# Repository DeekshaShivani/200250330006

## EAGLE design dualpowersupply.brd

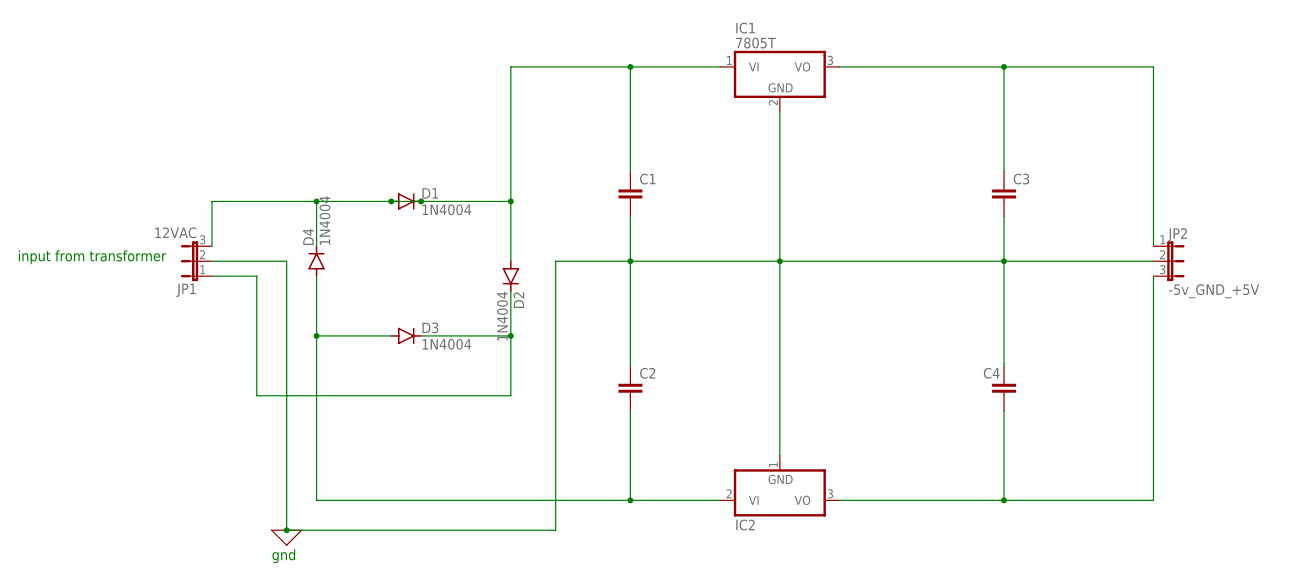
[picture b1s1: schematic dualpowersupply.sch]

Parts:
C1, C2, C3, C4: C2,5-3; C2.5-3
D1, D2, D3, D4: 1N4004; DO41-10
IC1: 7805T; TO220H
IC2: 7905T; TO220H
JP1: 12VAC; JP2W
JP2: -5v_GND_+5V; JP2W

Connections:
0: C1.2, C2.1, C3.2, C4.1, IC1.2 (GND), IC2.1 (GND), JP1.2, JP2.2
unnamed: C1.1, D1.A, D1.C, D2.A, D4.C, IC1.1 (VI), JP1.3
unnamed: C2.2, D3.A, D4.A, IC2.2 (VI)
unnamed: D2.C, D3.C, JP1.1
unnamed: C3.1, IC1.3 (VO), JP2.1
unnamed: C4.2, IC2.3 (VO), JP2.3

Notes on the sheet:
gnd
input from transformer

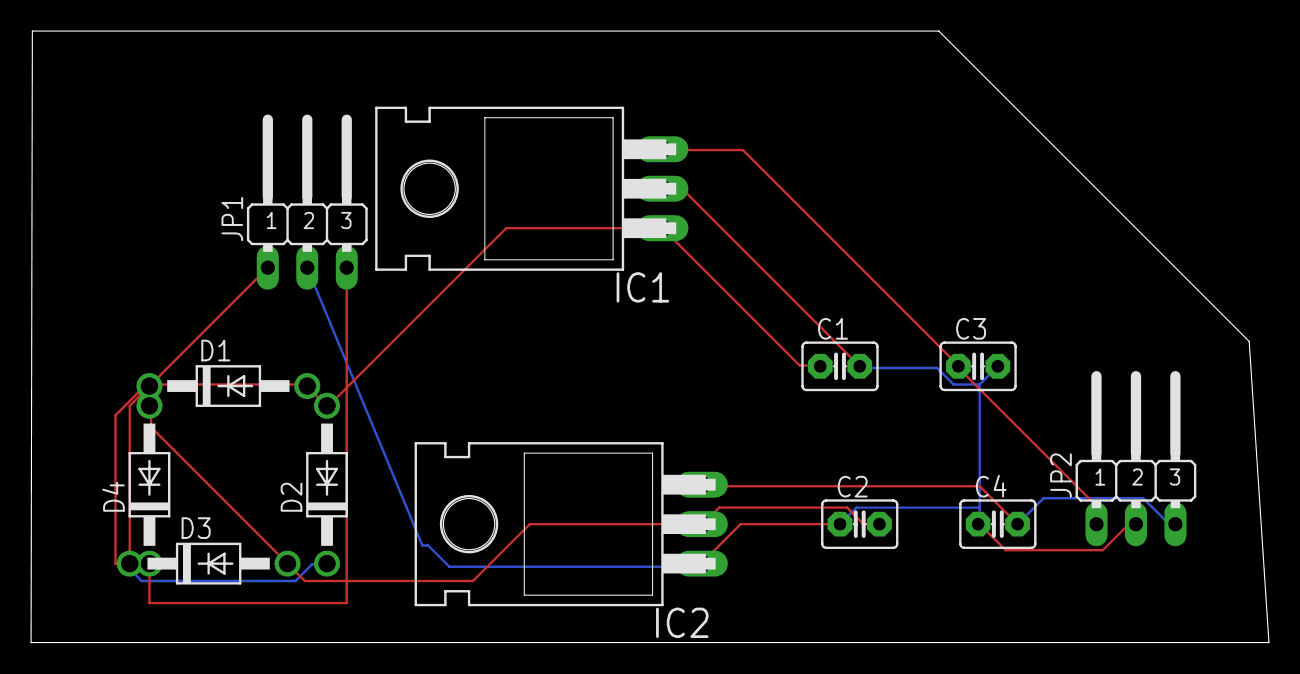
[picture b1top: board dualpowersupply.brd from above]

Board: 2 copper layers, 79.7 x 39.4 mm, 12 parts (0 on the bottom side), 6 nets.

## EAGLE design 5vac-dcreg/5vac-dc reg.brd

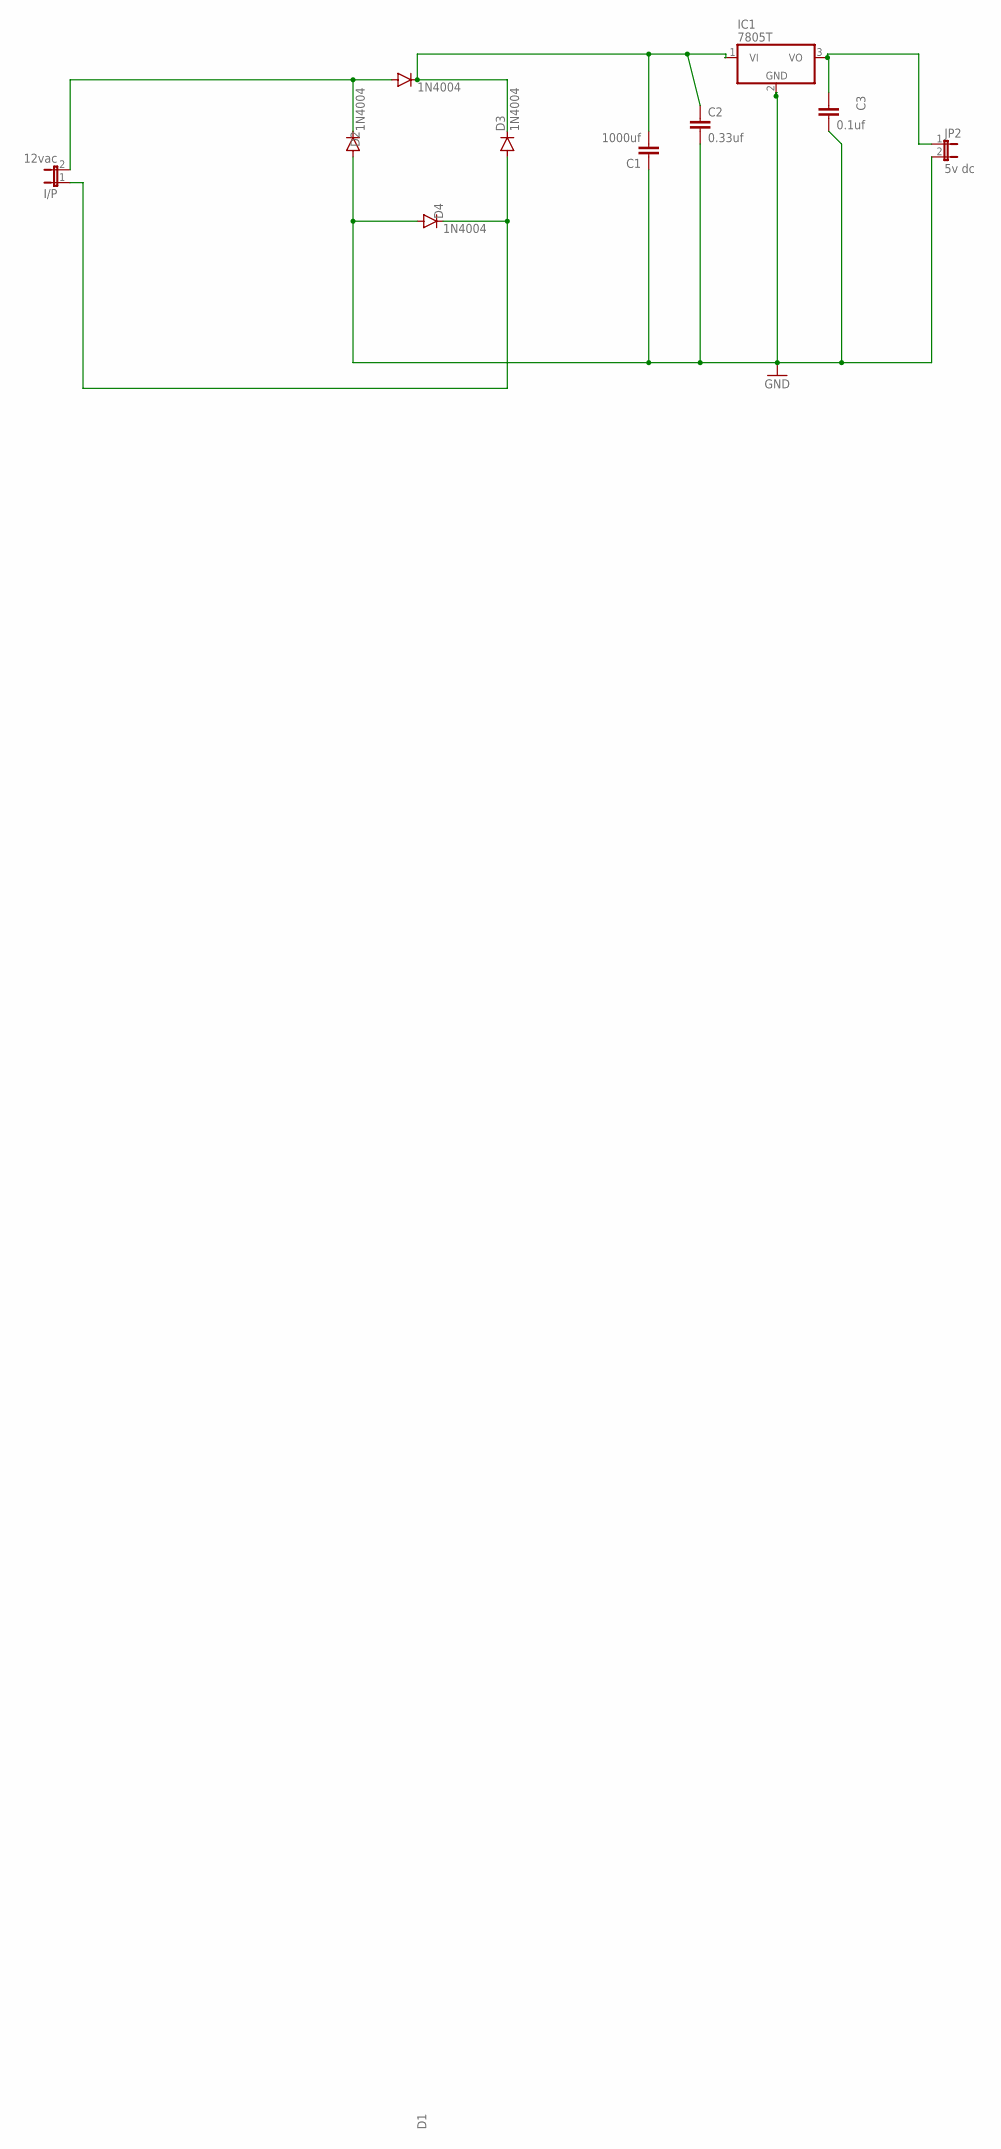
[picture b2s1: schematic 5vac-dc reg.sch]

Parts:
C1: 1000uf; C2.5-3
C2: 0.33uf; C2.5-3
C3: 0.1uf; C2.5-3
D1, D2, D3, D4: 1N4004; DO41-10
I/P: 12vac; JP1
IC1: 7805T; TO220H
JP2: 5v dc; JP1

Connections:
GND: C1.1, C2.2, C3.2, D2.A, D4.A, IC1.2 (GND), JP2.2
unnamed: D1.A, D2.C, I/P.2
unnamed: C3.1, IC1.3 (VO), JP2.1
unnamed: D3.A, D4.C, I/P.1
unnamed: C1.2, C2.1, D1.C, D3.C, IC1.1 (VI)

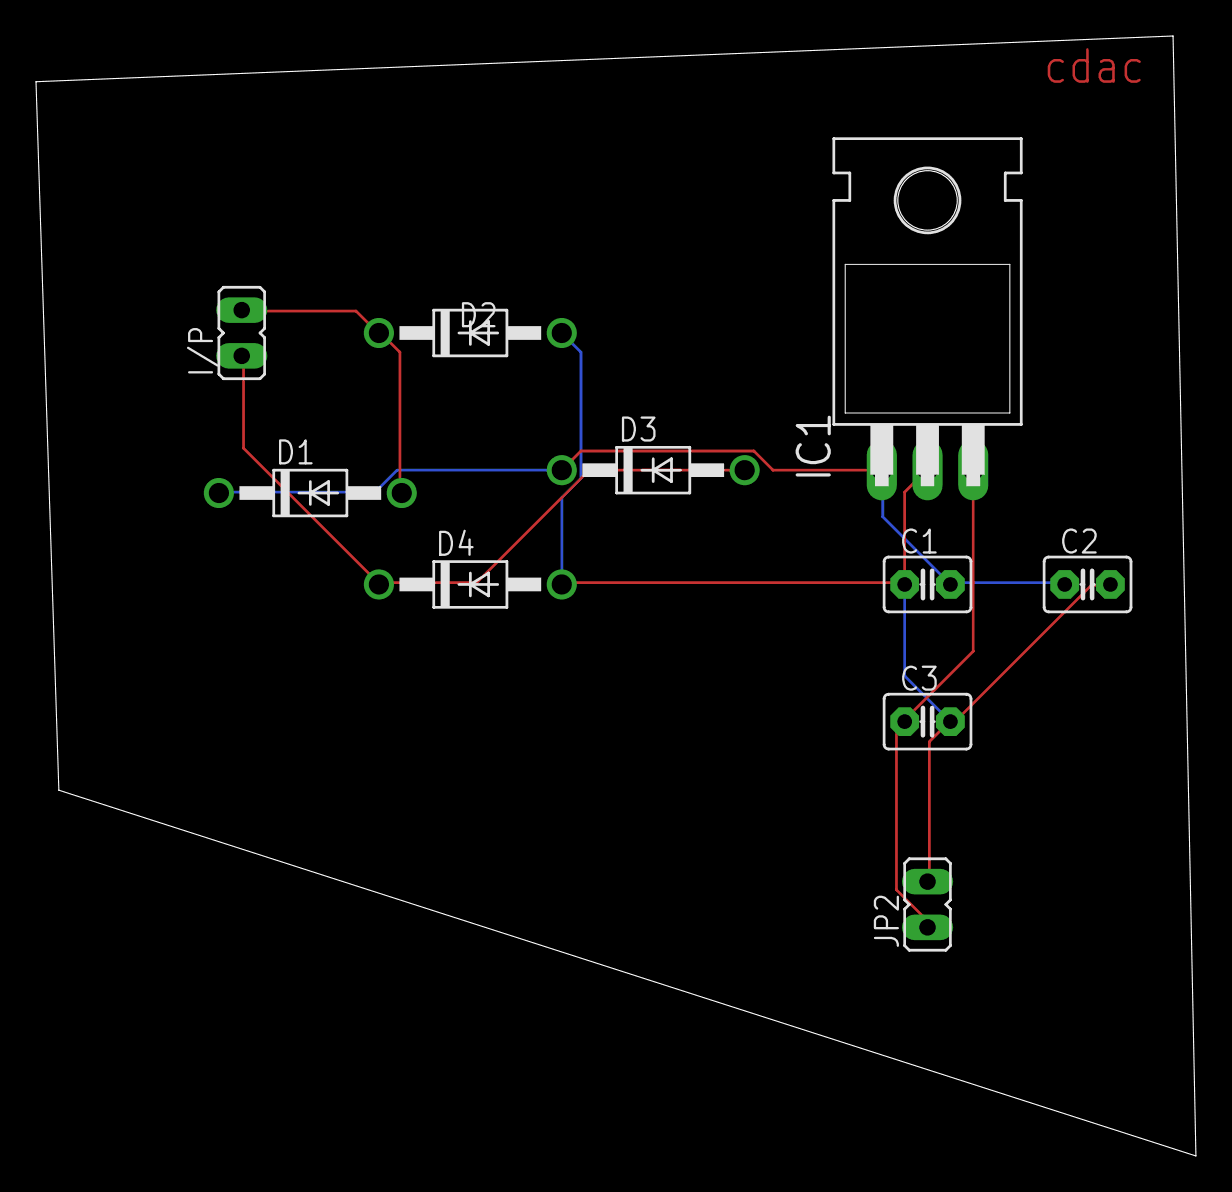
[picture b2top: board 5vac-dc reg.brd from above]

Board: 2 copper layers, 64.4 x 62.2 mm, 10 parts (0 on the bottom side), 5 nets.
